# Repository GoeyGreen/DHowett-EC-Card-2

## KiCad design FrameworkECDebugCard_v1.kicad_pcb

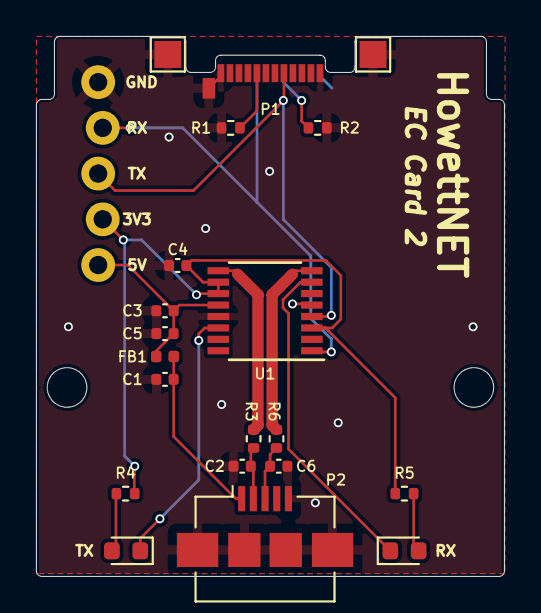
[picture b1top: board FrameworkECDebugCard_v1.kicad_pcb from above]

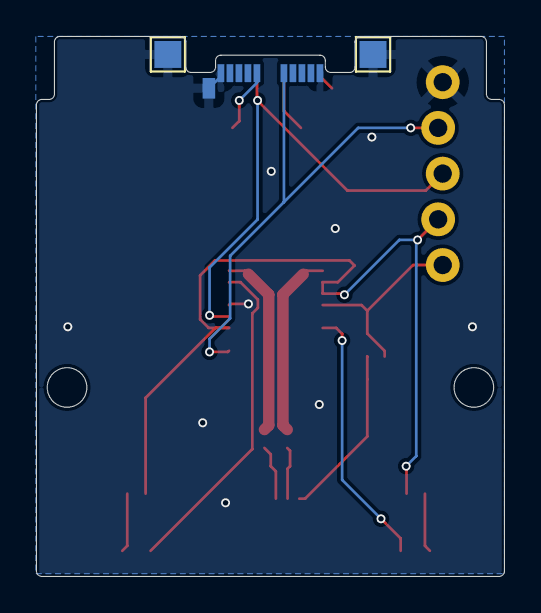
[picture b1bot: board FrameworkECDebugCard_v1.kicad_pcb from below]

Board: 2 copper layers, 26.0 x 30.0 mm, 25 parts (2 on the bottom side), 16 nets.

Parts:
C1: 10nf; C_0402_1005Metric
C2, C6: 47pF; C_0402_1005Metric
C3, C4: 100nf; C_0402_1005Metric
C5: 4.7uF; C_0402_1005Metric
D1: Red; LED_0603_1608Metric
D2: Green; LED_0603_1608Metric
FB1: 500mA; L_0402_1005Metric
H1, H2: MountingHole; MountingHole_2.2mm_M2
J1: Conn_01x05; 1X05_LOCK
P1: USB_C_Plug_USB2.0; USB_C_Plug_Molex_105444
P2: USB_B_Micro; USB_Micro-B_Amphenol_10104110_Horizontal
R1, R2: 5.1k; R_0402_1005Metric
R3, R6: 27R; R_0402_1005Metric
R4, R5: 270R; R_0402_1005Metric
TP1, TP2, TP3, TP4: TestPoint; TestPoint_Pad_1.5x1.5mm
U1: FT230XS; SSOP-16_3.9x4.9mm_P0.635mm

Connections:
/DIN: J1.4, P1.B8 (DIN), U1.1 (TXD)
/DOUT: J1.3, P1.A8 (DOUT), U1.4 (RXD)
/F_USBD+: R6.2, U1.8 (USBDP)
/F_USBD-: R3.2, U1.9 (USBDM)
/RXLED: D2.1 (K), U1.7 (CBUS2)
/TXLED: D1.1 (K), U1.14 (CBUS1)
/USBD+: C6.1, P2.3 (D+), R6.1
/USBD-: C2.1, P2.2 (D-), R3.1
GND: C1.2, C2.2, C3.2, C4.2, C5.2, C6.2, J1.5, P1.A1 (GND), P1.A12 (GND), P1.B1 (GND), P1.B12 (GND), P1.S1 (SHIELD), P2.5 (GND), P2.6 (Shield), R1.2, R2.2, TP1.1, TP2.1, TP3.1, TP4.1, U1.5 (GND), U1.13 (GND)
unnamed: C1.1, FB1.1, P2.1 (VBUS)
unnamed: D2.2 (A), R5.2
unnamed: D1.2 (A), R4.2
unnamed: P1.A5 (CC), R1.1
unnamed: P1.B5 (VCONN), R2.1
VBUS_HOST: C3.1, C5.1, FB1.2, J1.1, U1.12 (VCC)
VCCIO: C4.1, J1.2, R4.1, R5.1, U1.3 (VCCIO), U1.10 (3V3OUT), U1.11 (~RESET)

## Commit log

2024-03-01 Create folder
